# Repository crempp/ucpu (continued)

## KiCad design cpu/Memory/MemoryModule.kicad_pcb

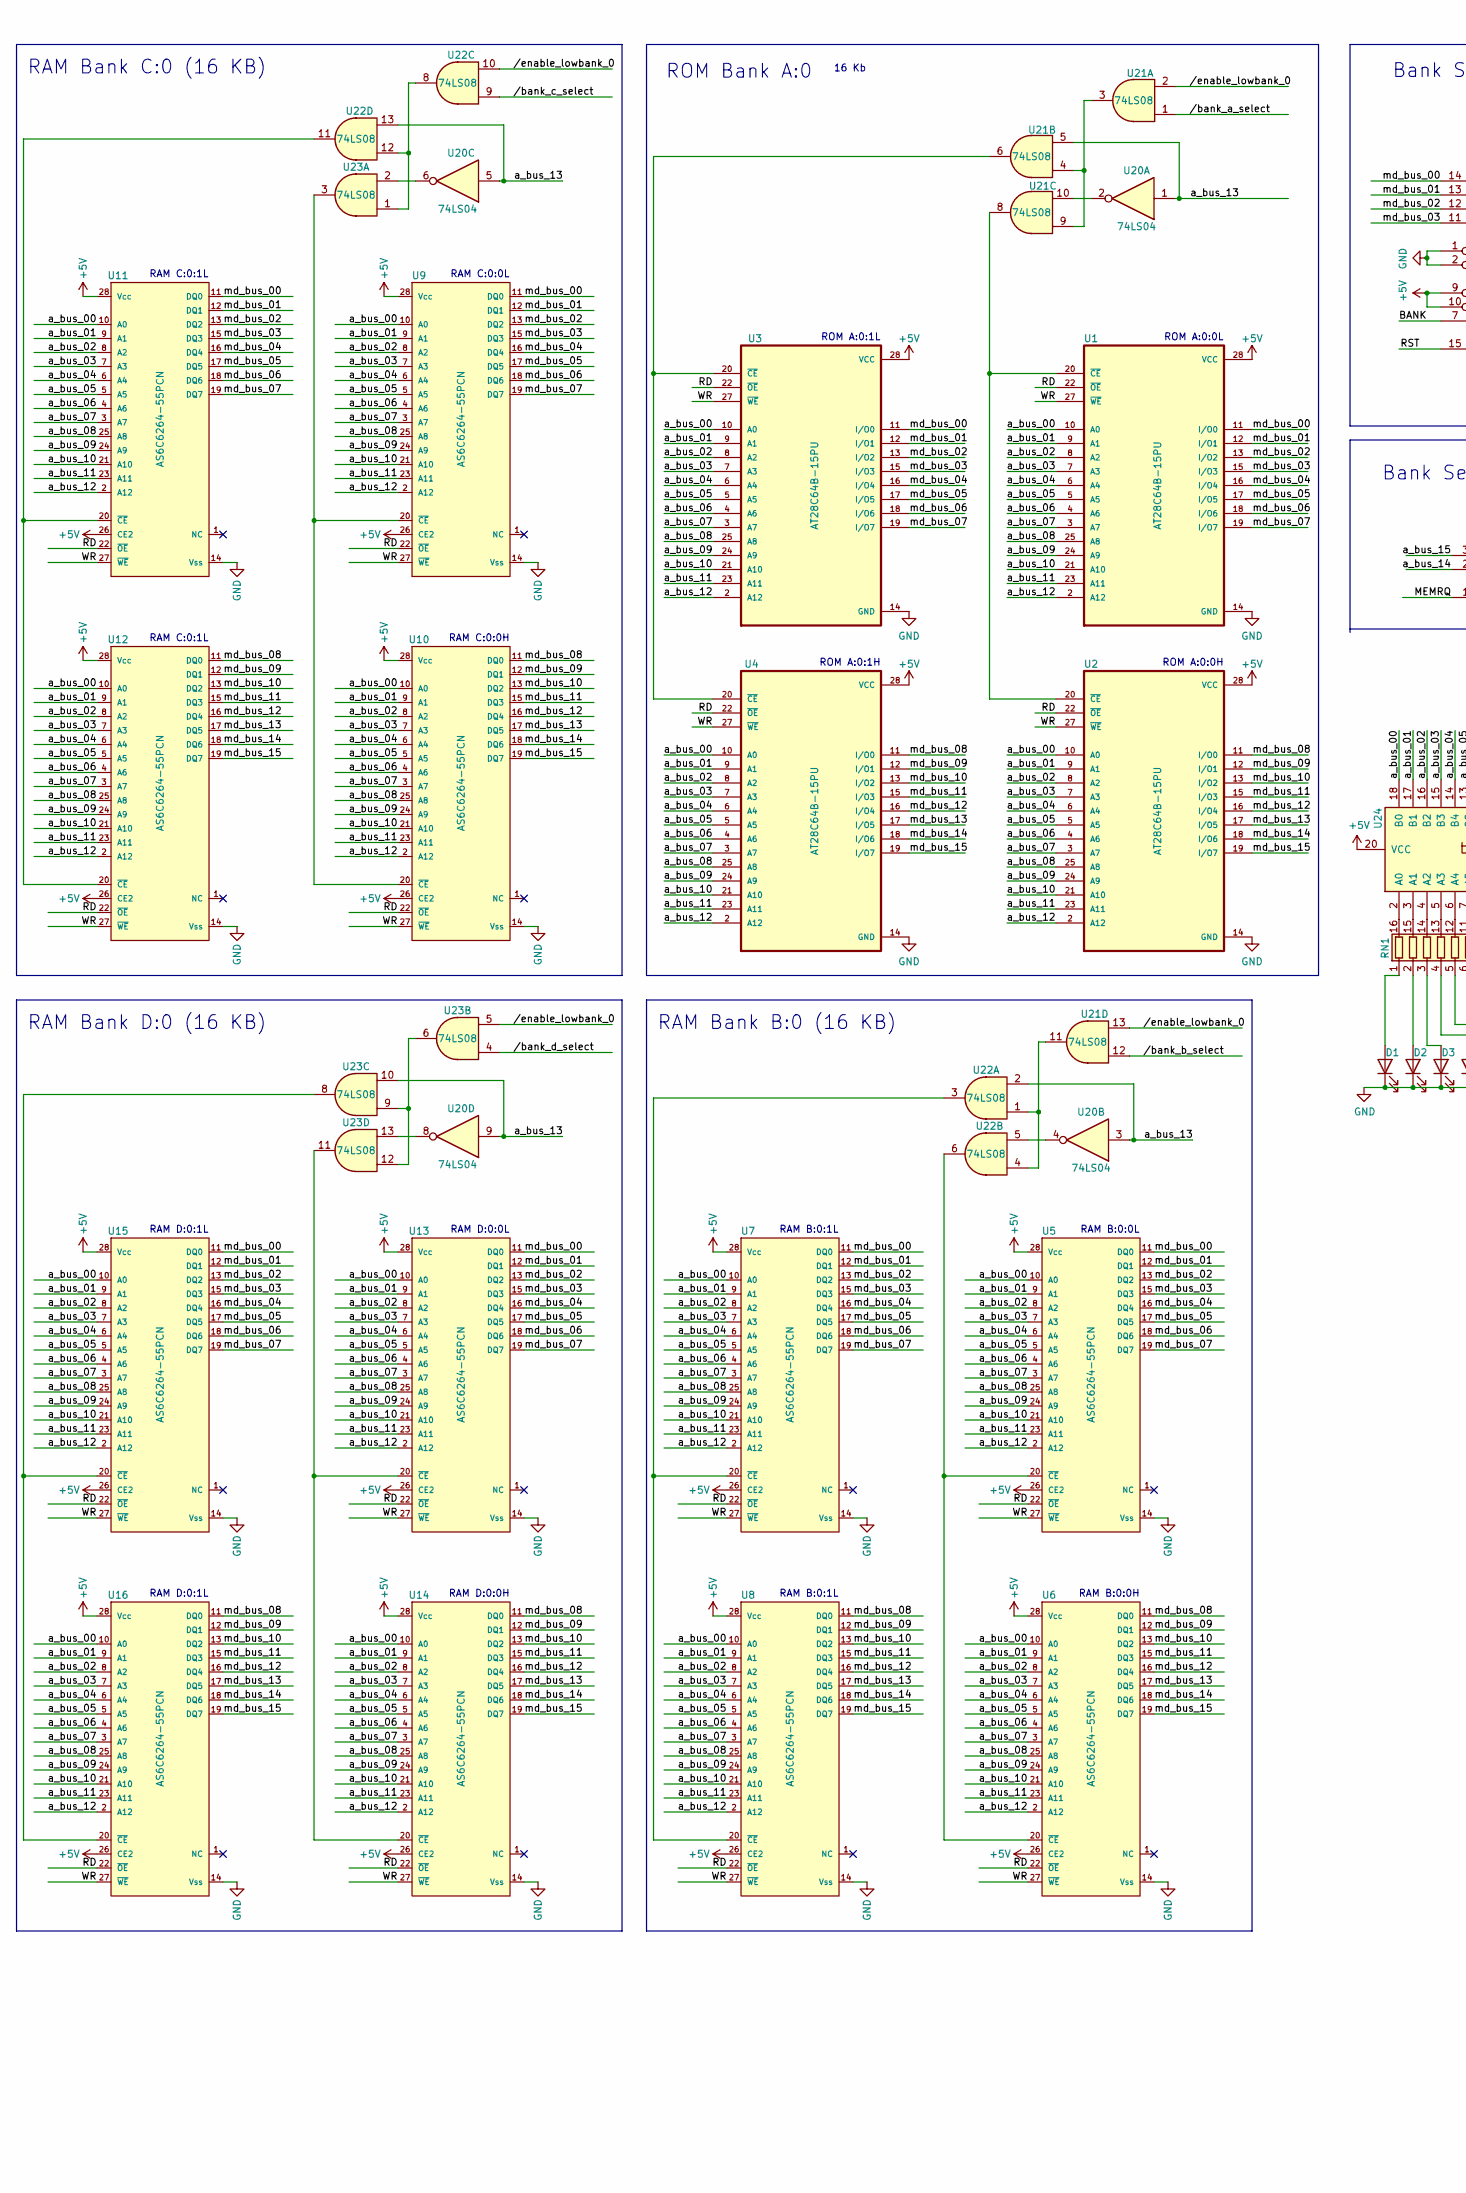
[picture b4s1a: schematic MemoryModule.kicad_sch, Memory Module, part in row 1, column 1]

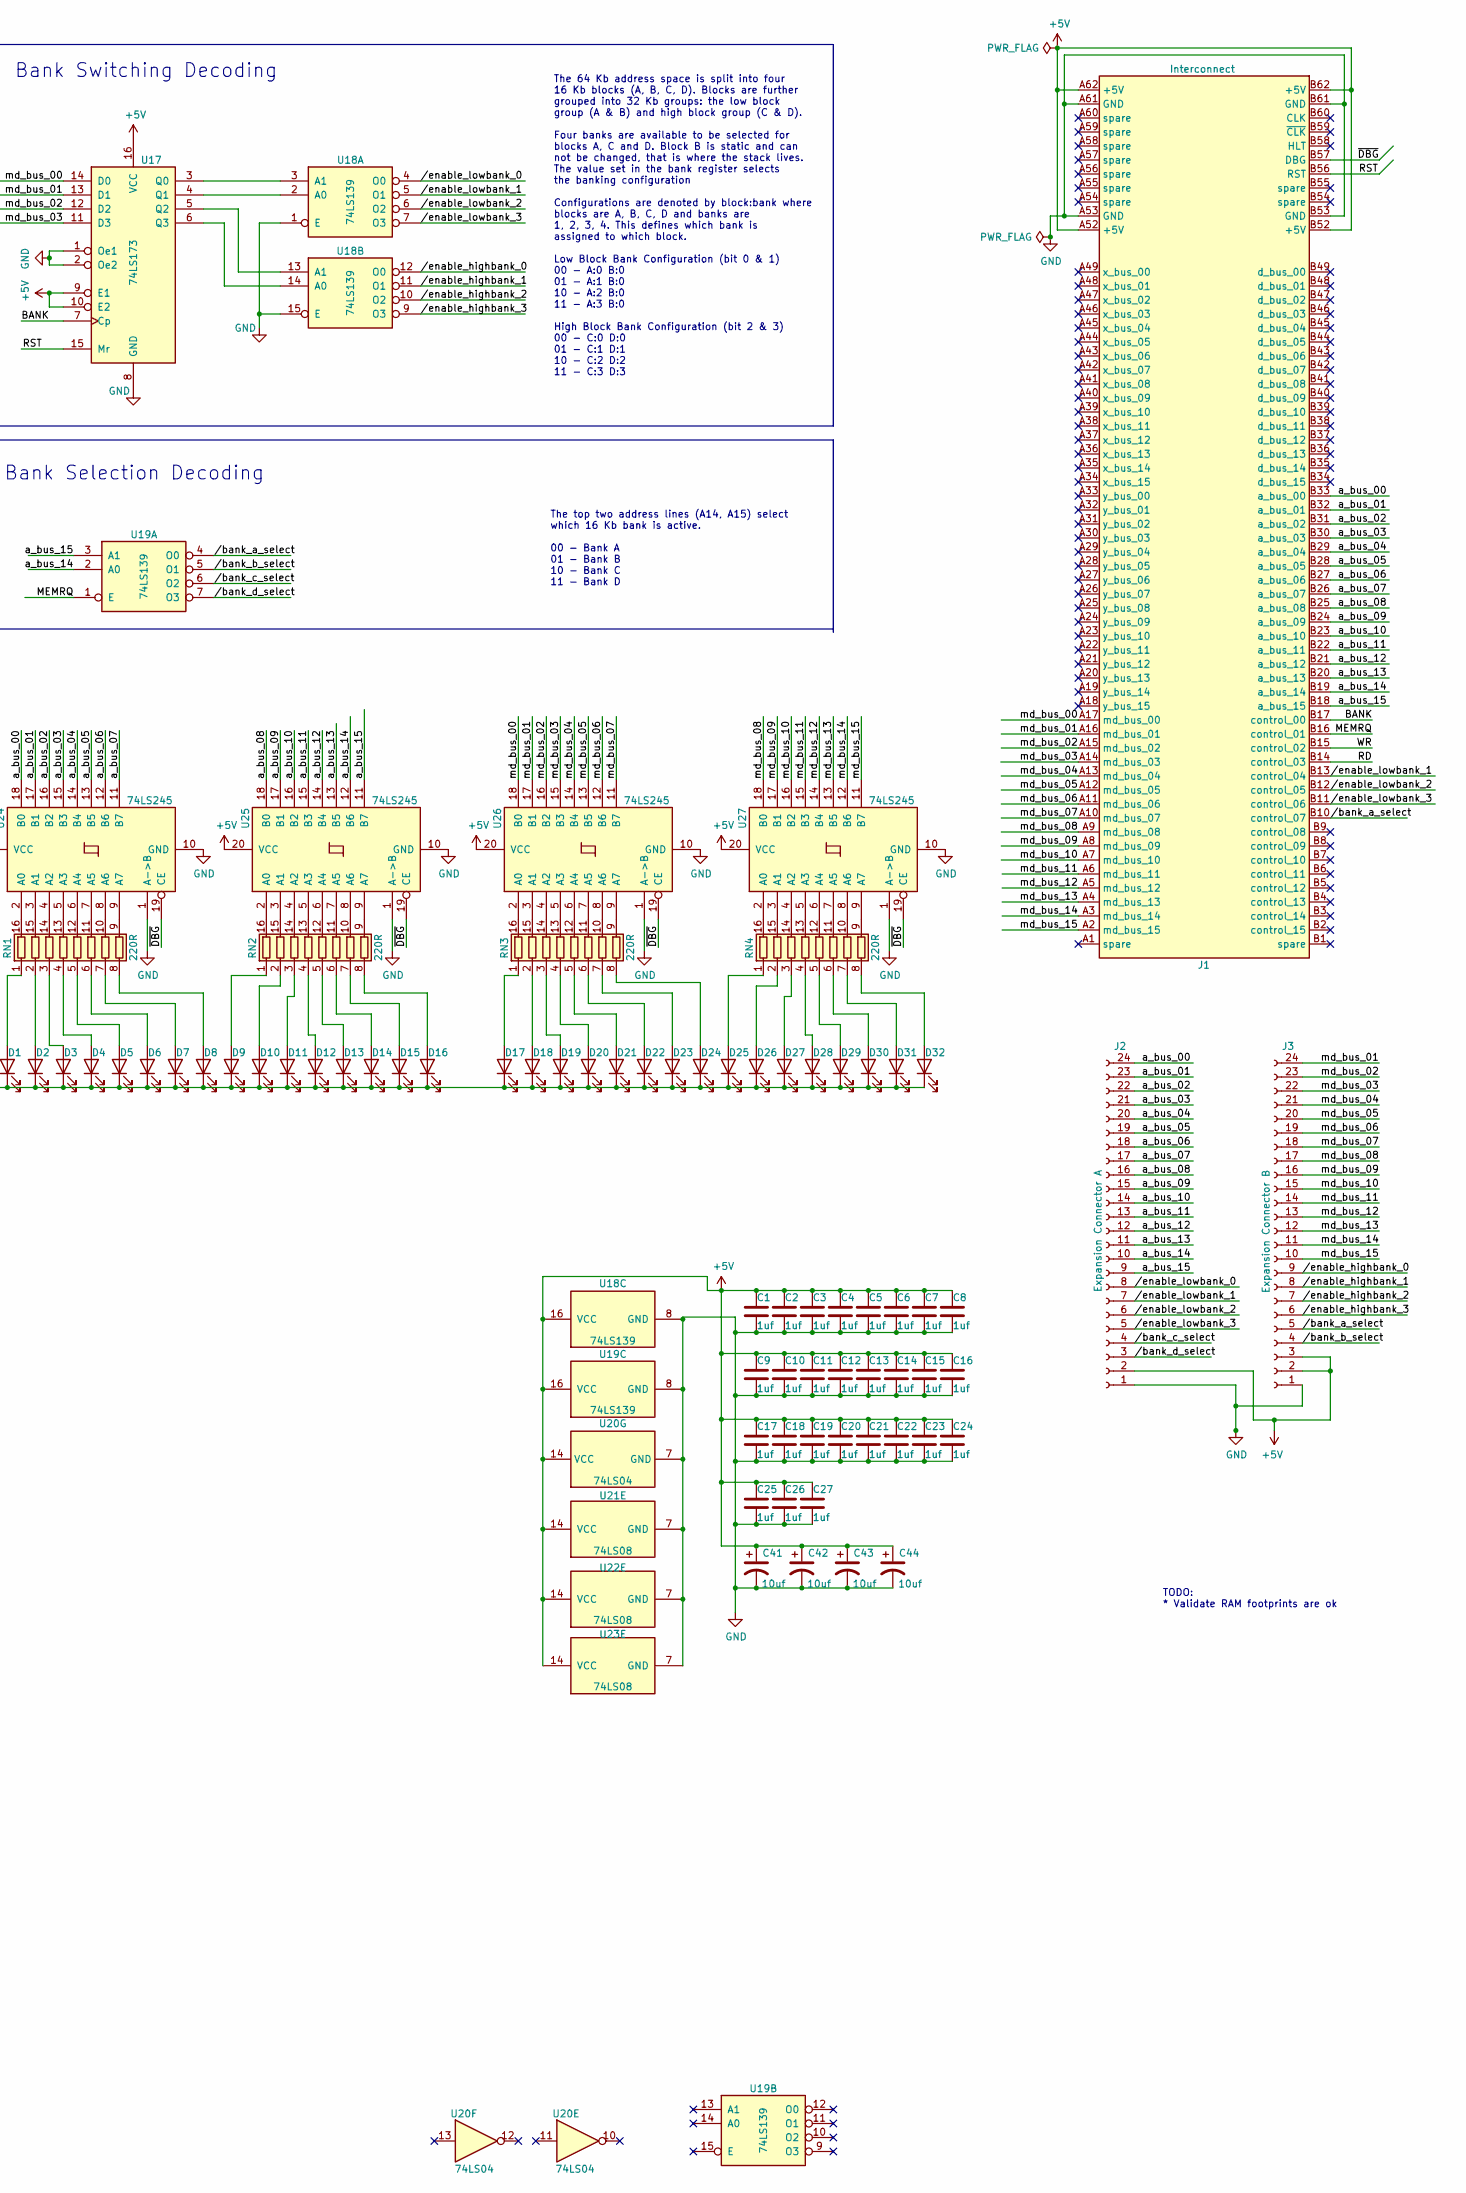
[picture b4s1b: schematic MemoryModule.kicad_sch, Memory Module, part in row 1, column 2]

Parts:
C1, C2, C3, C4, C5, C6, C7, C8, C9, C10, C11, C12, C13, C14, C15, C16, C17, C18, C19, C20, C21, C22, C23, C24, C25, C26, C27: 1uf; C_0603_1608Metric_Pad1.08x0.95mm_HandSolder
C41, C42, C43, C44: 10uf; CP_Elec_4x5.4
D1, D2, D3, D4, D5, D6, D7, D8, D9, D10, D11, D12, D13, D14, D15, D16, D17, D18, D19, D20, D21, D22, D23, D24, D25, D26, D27, D28, D29, D30, D31, D32: LED; LED_1206_3216Metric_Pad1.42x1.75mm_HandSolder
J1: Interconnect; BUS_PCI
J2: Expansion Connector A; PinHeader_1x24_P1.27mm_Vertical
J3: Expansion Connector B; PinHeader_1x24_P1.27mm_Vertical
RN1, RN2, RN3, RN4: 220R; R_Array_Convex_8x0602; Digikey Y1221CT-ND
U1, U2, U3, U4: AT28C64B-15PU; DIP-28_W15.24mm
U5, U6, U7, U8, U9, U10, U11, U12, U13, U14, U15, U16: AS6C6264-55PCN; SOIC-28W_7.5x18.7mm_P1.27mm; mouser part number 913-AS6C6264-55PCN; digikey description IC SRAM 64K PARALLEL 28DIP
U17: 74LS173; SOIC-16_3.9x9.9mm_P1.27mm
U18, U19: 74LS139; SOIC-16_3.9x9.9mm_P1.27mm
U20: 74LS04; SOIC-14_3.9x8.7mm_P1.27mm
U21, U22, U23: 74LS08; SOIC-14_3.9x8.7mm_P1.27mm
U24, U25, U26, U27: 74LS245; SOIC-20W_7.5x12.8mm_P1.27mm; Digikey 296-1208-1-ND

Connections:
+5V: C1.1, C2.1, C3.1, C4.1, C5.1, C6.1, C7.1, C8.1, C9.1, C10.1, C11.1, C12.1, C13.1, C14.1, C15.1, C16.1, C17.1, C18.1, C19.1, C20.1, C21.1, C22.1, C23.1, C24.1, C25.1, C26.1, C27.1, C41.1, C42.1, C43.1, C44.1, J1.A52 (+5V), J1.A62 (+5V), J1.B52 (+5V), J1.B62 (+5V), J2.2, J3.2, J3.3, U1.28 (VCC), U2.28 (VCC), U3.28 (VCC), U4.28 (VCC), U5.26 (CE2), U5.28 (Vcc), U6.26 (CE2), U6.28 (Vcc), U7.26 (CE2), U7.28 (Vcc), U8.26 (CE2), U8.28 (Vcc), U9.26 (CE2), U9.28 (Vcc), U10.26 (CE2), U10.28 (Vcc), U11.26 (CE2), U11.28 (Vcc), U12.26 (CE2), U12.28 (Vcc), U13.26 (CE2), U13.28 (Vcc), U14.26 (CE2), U14.28 (Vcc), U15.26 (CE2), U15.28 (Vcc), U16.26 (CE2), U16.28 (Vcc), U17.9 (E1), U17.10 (E2), U17.16 (VCC), U18.16 (VCC), U19.16 (VCC), U20.14 (VCC), U21.14 (VCC), U22.14 (VCC), U23.14 (VCC), U24.20 (VCC), U25.20 (VCC), U26.20 (VCC), U27.20 (VCC)
/BANK: J1.B17 (control_00), U17.7 (Cp)
/MEMRQ: J1.B16 (control_01), U19.1 (E)
/RD: J1.B14 (control_03), U1.22 (~OE), U2.22 (~OE), U3.22 (~OE), U4.22 (~OE), U5.22 (~OE), U6.22 (~OE), U7.22 (~OE), U8.22 (~OE), U9.22 (~OE), U10.22 (~OE), U11.22 (~OE), U12.22 (~OE), U13.22 (~OE), U14.22 (~OE), U15.22 (~OE), U16.22 (~OE)
/RST: J1.B56 (RST), U17.15 (Mr)
/WR: J1.B15 (control_02), U1.27 (~WE), U2.27 (~WE), U3.27 (~WE), U4.27 (~WE), U5.27 (~WE), U6.27 (~WE), U7.27 (~WE), U8.27 (~WE), U9.27 (~WE), U10.27 (~WE), U11.27 (~WE), U12.27 (~WE), U13.27 (~WE), U14.27 (~WE), U15.27 (~WE), U16.27 (~WE)
/a_bus_00: J1.B33 (a_bus_00), J2.24, U1.10 (A0), U2.10 (A0), U3.10 (A0), U4.10 (A0), U5.10 (A0), U6.10 (A0), U7.10 (A0), U8.10 (A0), U9.10 (A0), U10.10 (A0), U11.10 (A0), U12.10 (A0), U13.10 (A0), U14.10 (A0), U15.10 (A0), U16.10 (A0), U24.18 (B0)
/a_bus_01: J1.B32 (a_bus_01), J2.23, U1.9 (A1), U2.9 (A1), U3.9 (A1), U4.9 (A1), U5.9 (A1), U6.9 (A1), U7.9 (A1), U8.9 (A1), U9.9 (A1), U10.9 (A1), U11.9 (A1), U12.9 (A1), U13.9 (A1), U14.9 (A1), U15.9 (A1), U16.9 (A1), U24.17 (B1)
/a_bus_02: J1.B31 (a_bus_02), J2.22, U1.8 (A2), U2.8 (A2), U3.8 (A2), U4.8 (A2), U5.8 (A2), U6.8 (A2), U7.8 (A2), U8.8 (A2), U9.8 (A2), U10.8 (A2), U11.8 (A2), U12.8 (A2), U13.8 (A2), U14.8 (A2), U15.8 (A2), U16.8 (A2), U24.16 (B2)
/a_bus_03: J1.B30 (a_bus_03), J2.21, U1.7 (A3), U2.7 (A3), U3.7 (A3), U4.7 (A3), U5.7 (A3), U6.7 (A3), U7.7 (A3), U8.7 (A3), U9.7 (A3), U10.7 (A3), U11.7 (A3), U12.7 (A3), U13.7 (A3), U14.7 (A3), U15.7 (A3), U16.7 (A3), U24.15 (B3)
/a_bus_04: J1.B29 (a_bus_04), J2.20, U1.6 (A4), U2.6 (A4), U3.6 (A4), U4.6 (A4), U5.6 (A4), U6.6 (A4), U7.6 (A4), U8.6 (A4), U9.6 (A4), U10.6 (A4), U11.6 (A4), U12.6 (A4), U13.6 (A4), U14.6 (A4), U15.6 (A4), U16.6 (A4), U24.14 (B4)
/a_bus_05: J1.B28 (a_bus_05), J2.19, U1.5 (A5), U2.5 (A5), U3.5 (A5), U4.5 (A5), U5.5 (A5), U6.5 (A5), U7.5 (A5), U8.5 (A5), U9.5 (A5), U10.5 (A5), U11.5 (A5), U12.5 (A5), U13.5 (A5), U14.5 (A5), U15.5 (A5), U16.5 (A5), U24.13 (B5)
/a_bus_06: J1.B27 (a_bus_06), J2.18, U1.4 (A6), U2.4 (A6), U3.4 (A6), U4.4 (A6), U5.4 (A6), U6.4 (A6), U7.4 (A6), U8.4 (A6), U9.4 (A6), U10.4 (A6), U11.4 (A6), U12.4 (A6), U13.4 (A6), U14.4 (A6), U15.4 (A6), U16.4 (A6), U24.12 (B6)
/a_bus_07: J1.B26 (a_bus_07), J2.17, U1.3 (A7), U2.3 (A7), U3.3 (A7), U4.3 (A7), U5.3 (A7), U6.3 (A7), U7.3 (A7), U8.3 (A7), U9.3 (A7), U10.3 (A7), U11.3 (A7), U12.3 (A7), U13.3 (A7), U14.3 (A7), U15.3 (A7), U16.3 (A7), U24.11 (B7)
/a_bus_08: J1.B25 (a_bus_08), J2.16, U1.25 (A8), U2.25 (A8), U3.25 (A8), U4.25 (A8), U5.25 (A8), U6.25 (A8), U7.25 (A8), U8.25 (A8), U9.25 (A8), U10.25 (A8), U11.25 (A8), U12.25 (A8), U13.25 (A8), U14.25 (A8), U15.25 (A8), U16.25 (A8), U25.18 (B0)
/a_bus_09: J1.B24 (a_bus_09), J2.15, U1.24 (A9), U2.24 (A9), U3.24 (A9), U4.24 (A9), U5.24 (A9), U6.24 (A9), U7.24 (A9), U8.24 (A9), U9.24 (A9), U10.24 (A9), U11.24 (A9), U12.24 (A9), U13.24 (A9), U14.24 (A9), U15.24 (A9), U16.24 (A9), U25.17 (B1)
/a_bus_10: J1.B23 (a_bus_10), J2.14, U1.21 (A10), U2.21 (A10), U3.21 (A10), U4.21 (A10), U5.21 (A10), U6.21 (A10), U7.21 (A10), U8.21 (A10), U9.21 (A10), U10.21 (A10), U11.21 (A10), U12.21 (A10), U13.21 (A10), U14.21 (A10), U15.21 (A10), U16.21 (A10), U25.16 (B2)
/a_bus_11: J1.B22 (a_bus_11), J2.13, U1.23 (A11), U2.23 (A11), U3.23 (A11), U4.23 (A11), U5.23 (A11), U6.23 (A11), U7.23 (A11), U8.23 (A11), U9.23 (A11), U10.23 (A11), U11.23 (A11), U12.23 (A11), U13.23 (A11), U14.23 (A11), U15.23 (A11), U16.23 (A11), U25.15 (B3)
/a_bus_12: J1.B21 (a_bus_12), J2.12, U1.2 (A12), U2.2 (A12), U3.2 (A12), U4.2 (A12), U5.2 (A12), U6.2 (A12), U7.2 (A12), U8.2 (A12), U9.2 (A12), U10.2 (A12), U11.2 (A12), U12.2 (A12), U13.2 (A12), U14.2 (A12), U15.2 (A12), U16.2 (A12), U25.14 (B4)
/a_bus_13: J1.B20 (a_bus_13), J2.11, U20.1, U20.3, U20.5, U20.9, U21.5, U22.2, U22.13, U23.10, U25.13 (B5)
/a_bus_14: J1.B19 (a_bus_14), J2.10, U19.2 (A0), U25.12 (B6)
/a_bus_15: J1.B18 (a_bus_15), J2.9, U19.3 (A1), U25.11 (B7)
/md_bus_00: J1.A17 (md_bus_00), U1.11 (I/O0), U3.11 (I/O0), U5.11 (DQ0), U7.11 (DQ0), U9.11 (DQ0), U11.11 (DQ0), U13.11 (DQ0), U15.11 (DQ0), U17.14 (D0), U26.18 (B0)
/md_bus_01: J1.A16 (md_bus_01), J3.24, U1.12 (I/O1), U3.12 (I/O1), U5.12 (DQ1), U7.12 (DQ1), U9.12 (DQ1), U11.12 (DQ1), U13.12 (DQ1), U15.12 (DQ1), U17.13 (D1), U26.17 (B1)
/md_bus_02: J1.A15 (md_bus_02), J3.23, U1.13 (I/O2), U3.13 (I/O2), U5.13 (DQ2), U7.13 (DQ2), U9.13 (DQ2), U11.13 (DQ2), U13.13 (DQ2), U15.13 (DQ2), U17.12 (D2), U26.16 (B2)
/md_bus_03: J1.A14 (md_bus_03), J3.22, U1.15 (I/O3), U3.15 (I/O3), U5.15 (DQ3), U7.15 (DQ3), U9.15 (DQ3), U11.15 (DQ3), U13.15 (DQ3), U15.15 (DQ3), U17.11 (D3), U26.15 (B3)
/md_bus_04: J1.A13 (md_bus_04), J3.21, U1.16 (I/O4), U3.16 (I/O4), U5.16 (DQ4), U7.16 (DQ4), U9.16 (DQ4), U11.16 (DQ4), U13.16 (DQ4), U15.16 (DQ4), U26.14 (B4)
/md_bus_05: J1.A12 (md_bus_05), J3.20, U1.17 (I/O5), U3.17 (I/O5), U5.17 (DQ5), U7.17 (DQ5), U9.17 (DQ5), U11.17 (DQ5), U13.17 (DQ5), U15.17 (DQ5), U26.13 (B5)
/md_bus_06: J1.A11 (md_bus_06), J3.19, U1.18 (I/O6), U3.18 (I/O6), U5.18 (DQ6), U7.18 (DQ6), U9.18 (DQ6), U11.18 (DQ6), U13.18 (DQ6), U15.18 (DQ6), U26.12 (B6)
/md_bus_07: J1.A10 (md_bus_07), J3.18, U1.19 (I/O7), U3.19 (I/O7), U5.19 (DQ7), U7.19 (DQ7), U9.19 (DQ7), U11.19 (DQ7), U13.19 (DQ7), U15.19 (DQ7), U26.11 (B7)
/md_bus_08: J1.A9 (md_bus_08), J3.17, U2.11 (I/O0), U4.11 (I/O0), U6.11 (DQ0), U8.11 (DQ0), U10.11 (DQ0), U12.11 (DQ0), U14.11 (DQ0), U16.11 (DQ0), U27.18 (B0)
/md_bus_09: J1.A8 (md_bus_09), J3.16, U2.12 (I/O1), U4.12 (I/O1), U6.12 (DQ1), U8.12 (DQ1), U10.12 (DQ1), U12.12 (DQ1), U14.12 (DQ1), U16.12 (DQ1), U27.17 (B1)
/md_bus_10: J1.A7 (md_bus_10), J3.15, U2.13 (I/O2), U4.13 (I/O2), U6.13 (DQ2), U8.13 (DQ2), U10.13 (DQ2), U12.13 (DQ2), U14.13 (DQ2), U16.13 (DQ2), U27.16 (B2)
/md_bus_11: J1.A6 (md_bus_11), J3.14, U2.15 (I/O3), U4.15 (I/O3), U6.15 (DQ3), U8.15 (DQ3), U10.15 (DQ3), U12.15 (DQ3), U14.15 (DQ3), U16.15 (DQ3), U27.15 (B3)
/md_bus_12: J1.A5 (md_bus_12), J3.13, U2.16 (I/O4), U4.16 (I/O4), U6.16 (DQ4), U8.16 (DQ4), U10.16 (DQ4), U12.16 (DQ4), U14.16 (DQ4), U16.16 (DQ4), U27.14 (B4)
/md_bus_13: J1.A4 (md_bus_13), J3.12, U2.17 (I/O5), U4.17 (I/O5), U6.17 (DQ5), U8.17 (DQ5), U10.17 (DQ5), U12.17 (DQ5), U14.17 (DQ5), U16.17 (DQ5), U27.13 (B5)
/md_bus_14: J1.A3 (md_bus_14), J3.11, U2.18 (I/O6), U4.18 (I/O6), U6.18 (DQ6), U8.18 (DQ6), U10.18 (DQ6), U12.18 (DQ6), U14.18 (DQ6), U16.18 (DQ6), U27.12 (B6)
/md_bus_15: J1.A2 (md_bus_15), J3.10, U2.19 (I/O7), U4.19 (I/O7), U6.19 (DQ7), U8.19 (DQ7), U10.19 (DQ7), U12.19 (DQ7), U14.19 (DQ7), U16.19 (DQ7), U27.11 (B7)
//bank_a_select: J1.B10 (control_07), J3.5, U19.4 (O0), U21.1
//bank_c_select: J2.4, U19.6 (O2), U22.9
//bank_d_select: J2.3, U19.7 (O3), U23.4
//enable_highbank_1: J3.8, U18.11 (O1)
//enable_highbank_2: J3.7, U18.10 (O2)
//enable_highbank_3: J3.6, U18.9 (O3)
//enable_lowbank_1: J1.B13 (control_04), J2.7, U18.5 (O1)
//enable_lowbank_2: J1.B12 (control_05), J2.6, U18.6 (O2)
//enable_lowbank_3: J1.B11 (control_06), J2.5, U18.7 (O3)
/~DBG: J1.B57 (DBG), U24.19 (CE), U25.19 (CE), U26.19 (CE), U27.19 (CE)
GND: C1.2, C2.2, C3.2, C4.2, C5.2, C6.2, C7.2, C8.2, C9.2, C10.2, C11.2, C12.2, C13.2, C14.2, C15.2, C16.2, C17.2, C18.2, C19.2, C20.2, C21.2, C22.2, C23.2, C24.2, C25.2, C26.2, C27.2, C41.2, C42.2, C43.2, C44.2, D1.1 (K), D2.1 (K), D3.1 (K), D4.1 (K), D5.1 (K), D6.1 (K), D7.1 (K), D8.1 (K), D9.1 (K), D10.1 (K), D11.1 (K), D12.1 (K), D13.1 (K), D14.1 (K), D15.1 (K), D16.1 (K), D17.1 (K), D18.1 (K), D19.1 (K), D20.1 (K), D21.1 (K), D22.1 (K), D23.1 (K), D24.1 (K), D25.1 (K), D26.1 (K), D27.1 (K), D28.1 (K), D29.1 (K), D30.1 (K), D31.1 (K), D32.1 (K), J1.A53 (GND), J1.A61 (GND), J1.B53 (GND), J1.B61 (GND), J2.1, J3.1, U1.14 (GND), U2.14 (GND), U3.14 (GND), U4.14 (GND), U5.14 (Vss), U6.14 (Vss), U7.14 (Vss), U8.14 (Vss), U9.14 (Vss), U10.14 (Vss), U11.14 (Vss), U12.14 (Vss), U13.14 (Vss), U14.14 (Vss), U15.14 (Vss), U16.14 (Vss), U17.1 (Oe1), U17.2 (Oe2), U17.8 (GND), U18.1 (E), U18.8 (GND), U18.15 (E), U19.8 (GND), U20.7 (GND), U21.7 (GND), U22.7 (GND), U23.7 (GND), U24.1 (A->B), U24.10 (GND), U25.1 (A->B), U25.10 (GND), U26.1 (A->B), U26.10 (GND), U27.1 (A->B), U27.10 (GND)
unnamed: D1.2 (A), RN1.1 (R1.1)
unnamed: D2.2 (A), RN1.2 (R2.1)
unnamed: D3.2 (A), RN1.3 (R3.1)
unnamed: D4.2 (A), RN1.4 (R4.1)
unnamed: D5.2 (A), RN1.5 (R5.1)
unnamed: D6.2 (A), RN1.6 (R6.1)
unnamed: D7.2 (A), RN1.7 (R7.1)
unnamed: D8.2 (A), RN1.8 (R8.1)
unnamed: D9.2 (A), RN2.1 (R1.1)
unnamed: D10.2 (A), RN2.2 (R2.1)
unnamed: D11.2 (A), RN2.3 (R3.1)
unnamed: D12.2 (A), RN2.4 (R4.1)
unnamed: D13.2 (A), RN2.5 (R5.1)
unnamed: D14.2 (A), RN2.6 (R6.1)
unnamed: D15.2 (A), RN2.7 (R7.1)
unnamed: D16.2 (A), RN2.8 (R8.1)
unnamed: D17.2 (A), RN3.1 (R1.1)
unnamed: D18.2 (A), RN3.2 (R2.1)
unnamed: D19.2 (A), RN3.3 (R3.1)
unnamed: D20.2 (A), RN3.4 (R4.1)
unnamed: D21.2 (A), RN3.5 (R5.1)
unnamed: D22.2 (A), RN3.6 (R6.1)
unnamed: D23.2 (A), RN3.7 (R7.1)
unnamed: D24.2 (A), RN3.8 (R8.1)
unnamed: D25.2 (A), RN4.1 (R1.1)
unnamed: D26.2 (A), RN4.2 (R2.1)
unnamed: D27.2 (A), RN4.3 (R3.1)
unnamed: D28.2 (A), RN4.4 (R4.1)
unnamed: D29.2 (A), RN4.5 (R5.1)
unnamed: D30.2 (A), RN4.6 (R6.1)
unnamed: D31.2 (A), RN4.7 (R7.1)
unnamed: D32.2 (A), RN4.8 (R8.1)
unnamed: RN1.9 (R8.2), U24.9 (A7)
unnamed: RN1.10 (R7.2), U24.8 (A6)
unnamed: RN1.11 (R6.2), U24.7 (A5)
unnamed: RN1.12 (R5.2), U24.6 (A4)
unnamed: RN1.13 (R4.2), U24.5 (A3)
unnamed: RN1.14 (R3.2), U24.4 (A2)
unnamed: RN1.15 (R2.2), U24.3 (A1)
unnamed: RN1.16 (R1.2), U24.2 (A0)
unnamed: RN2.9 (R8.2), U25.9 (A7)
unnamed: RN2.10 (R7.2), U25.8 (A6)
unnamed: RN2.11 (R6.2), U25.7 (A5)
unnamed: RN2.12 (R5.2), U25.6 (A4)
unnamed: RN2.13 (R4.2), U25.5 (A3)
unnamed: RN2.14 (R3.2), U25.4 (A2)
unnamed: RN2.15 (R2.2), U25.3 (A1)
unnamed: RN2.16 (R1.2), U25.2 (A0)
unnamed: RN3.9 (R8.2), U26.9 (A7)
unnamed: RN3.10 (R7.2), U26.8 (A6)
unnamed: RN3.11 (R6.2), U26.7 (A5)
unnamed: RN3.12 (R5.2), U26.6 (A4)
unnamed: RN3.13 (R4.2), U26.5 (A3)
unnamed: RN3.14 (R3.2), U26.4 (A2)
unnamed: RN3.15 (R2.2), U26.3 (A1)
unnamed: RN3.16 (R1.2), U26.2 (A0)
unnamed: RN4.9 (R8.2), U27.9 (A7)
unnamed: RN4.10 (R7.2), U27.8 (A6)
unnamed: RN4.11 (R6.2), U27.7 (A5)
unnamed: RN4.12 (R5.2), U27.6 (A4)
unnamed: RN4.13 (R4.2), U27.5 (A3)
unnamed: RN4.14 (R3.2), U27.4 (A2)
unnamed: RN4.15 (R2.2), U27.3 (A1)
unnamed: RN4.16 (R1.2), U27.2 (A0)
unnamed: U1.20 (~CE), U2.20 (~CE), U21.8
unnamed: U9.20 (~CE), U10.20 (~CE), U23.3
unnamed: U11.20 (~CE), U12.20 (~CE), U22.11
unnamed: U13.20 (~CE), U14.20 (~CE), U23.11
unnamed: U15.20 (~CE), U16.20 (~CE), U23.8
unnamed: U17.3 (Q0), U18.3 (A1)
unnamed: U17.4 (Q1), U18.2 (A0)
unnamed: U17.5 (Q2), U18.13 (A1)
unnamed: U17.6 (Q3), U18.14 (A0)
unnamed: U20.2, U21.10
unnamed: U20.4, U22.5
unnamed: U20.6, U23.2
unnamed: U20.8, U23.13
unnamed: U21.3, U21.4, U21.9
unnamed: U3.20 (~CE), U4.20 (~CE), U21.6
unnamed: U7.20 (~CE), U8.20 (~CE), U22.3
unnamed: U5.20 (~CE), U6.20 (~CE), U22.6
unnamed: U22.8, U22.12, U23.1
unnamed: U23.6, U23.9, U23.12

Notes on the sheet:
RAM D:0:0L
ROM A:0:1L
The top two address lines (A14, A15) select which 16 Kb bank is active. 00 - Bank A 01 - Bank B 10 - Bank C 11 - Bank D
The 64 Kb address space is split into four 16 Kb blocks (A, B, C, D). Blocks are further grouped into 32 Kb groups: the low block group (A & B) and high block group (C & D). Four banks are available to be selected for blocks A, C and D. Block B is static and can not be changed, that is where the st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
RAM D:0:1L
Bank Selection Decoding
ROM A:0:0L
ROM Bank A:0
RAM C:0:1L
RAM Bank C:0 (16 KB)
Bank Switching Decoding
RAM Bank D:0 (16 KB)
RAM C:0:0H
RAM B:0:1L
RAM B:0:0L
RAM D:0:0H
ROM A:0:0H
RAM C:0:0L
RAM Bank B:0 (16 KB)
TODO: * Validate RAM footprints are ok
16 Kb
ROM A:0:1H
RAM B:0:0H

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
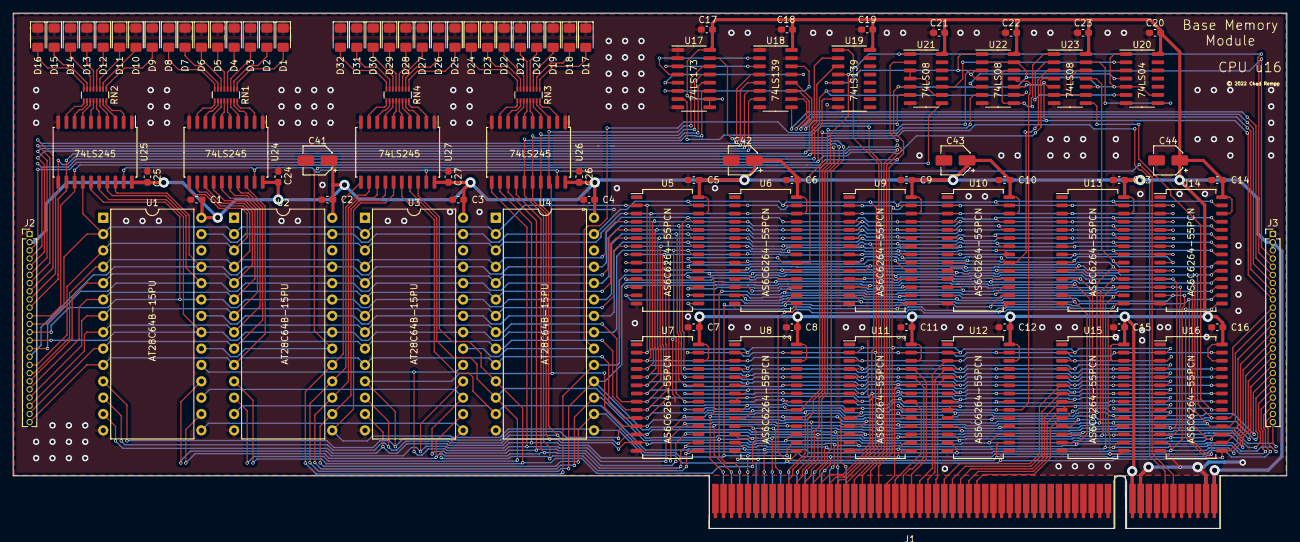
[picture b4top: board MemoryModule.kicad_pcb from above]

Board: 2 copper layers, 197.8 x 80.0 mm, 97 parts (0 on the bottom side), 135 nets.

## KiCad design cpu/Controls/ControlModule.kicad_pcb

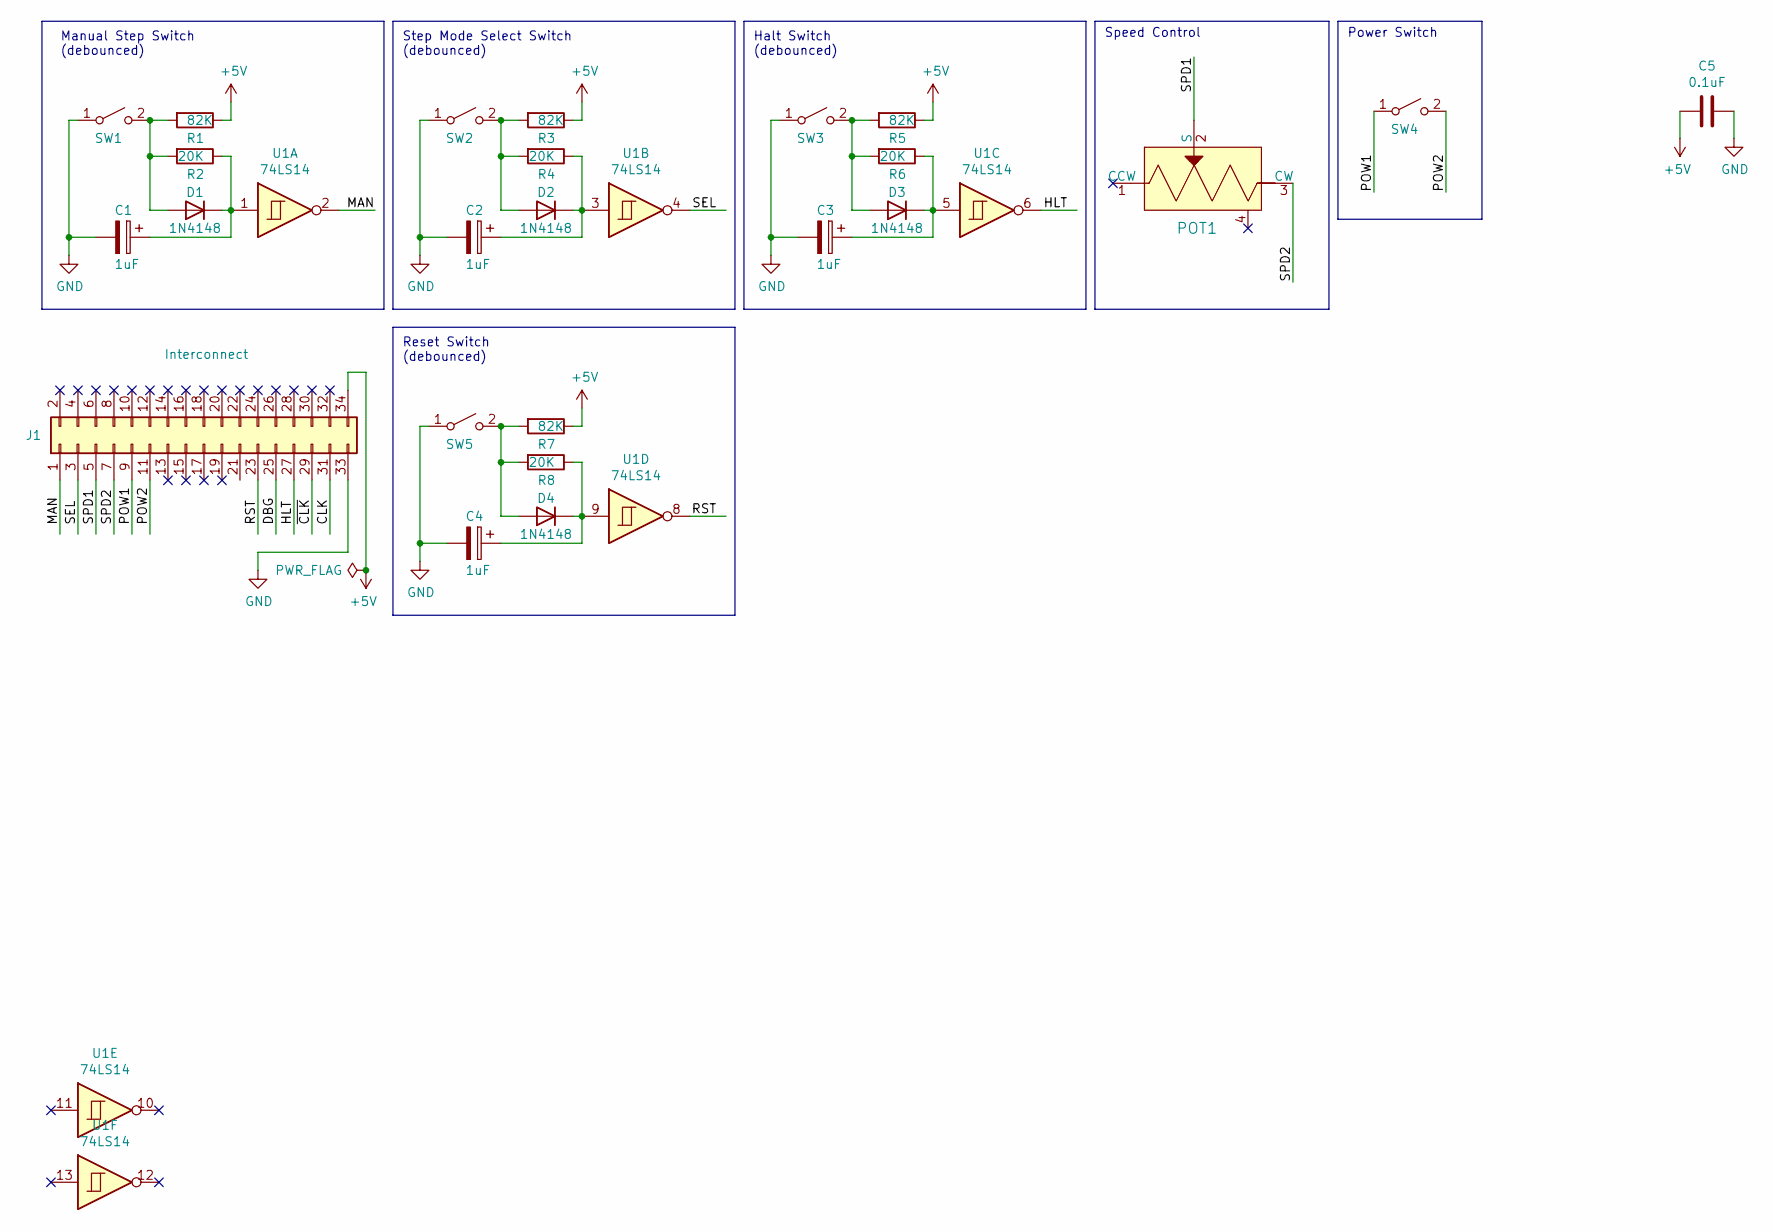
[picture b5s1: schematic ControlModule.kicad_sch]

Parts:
C1, C2, C3, C4: 1uF; CP_Elec_4x5.4; Digikey 493-9795-1-ND
C5: 0.1uF; C_0603_1608Metric_Pad1.05x0.95mm_HandSolder; Digikey 399-1096-1-ND
D1, D2, D3, D4: 1N4148; D_SOD-523; Digikey 1N4148XTPMSCT-ND
J1: Interconnect; PinHeader_2x17_P2.54mm_Horizontal; Digikey S5531-ND
POT1: P120PK-Y25BR10K; Potentiometer_P120PK-Y25BR10K; MPN P120PK-Y25BR10K; Digi-Key_PN 987-1710-ND
R1, R3, R5, R7: 82K; R_0603_1608Metric_Pad1.05x0.95mm_HandSolder; Digikey 311-82.0KHRCT-ND
R2, R4, R6, R8: 20K; R_0603_1608Metric_Pad1.05x0.95mm_HandSolder; Digikey 311-20.0KHRCT-ND
SW1, SW3, SW5: SW_SPST; SW_PUSH_6mm_H5mm; Digikey EG1861-ND
SW2, SW4: SW_SPST; SW_PUSH_6mm_H5mm; Digikey 401-1132-ND
U1: 74LS14; SOIC-14_3.9x8.7mm_P1.27mm; Digikey 296-14864-1-ND

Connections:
+5V: C5.2, J1.34, R1.1, R3.1, R5.1, R7.1
/CLK: J1.31
/DBG: J1.25
/HLT: J1.27, U1.6
/MAN: J1.1, U1.2
/POW1: J1.9, SW4.1 (A)
/POW2: J1.11, SW4.2 (B)
/RST: J1.23, U1.8
/SEL: J1.3, U1.4
/SPD1: J1.5, POT1.2 (S)
/SPD2: J1.7, POT1.3 (CW)
/~CLK: J1.29
GND: C1.2, C2.2, C3.2, C4.2, C5.1, J1.33, SW1.1 (A), SW2.1 (A), SW3.1 (A), SW5.1 (A)
unnamed: C1.1, D1.1 (K), R2.1, U1.1
unnamed: C2.1, D2.1 (K), R4.1, U1.3
unnamed: C3.1, D3.1 (K), R6.1, U1.5
unnamed: C4.1, D4.1 (K), R8.1, U1.9
unnamed: D1.2 (A), R1.2, R2.2, SW1.2 (B)
unnamed: D2.2 (A), R3.2, R4.2, SW2.2 (B)
unnamed: D3.2 (A), R5.2, R6.2, SW3.2 (B)
unnamed: D4.2 (A), R7.2, R8.2, SW5.2 (B)

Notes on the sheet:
Halt Switch (debounced)
Step Mode Select Switch (debounced)
Manual Step Switch (debounced)
Reset Switch (debounced)
Power Switch
Speed Control

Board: 2 copper layers, 25 parts (0 on the bottom side), 18 nets, no tracks yet.

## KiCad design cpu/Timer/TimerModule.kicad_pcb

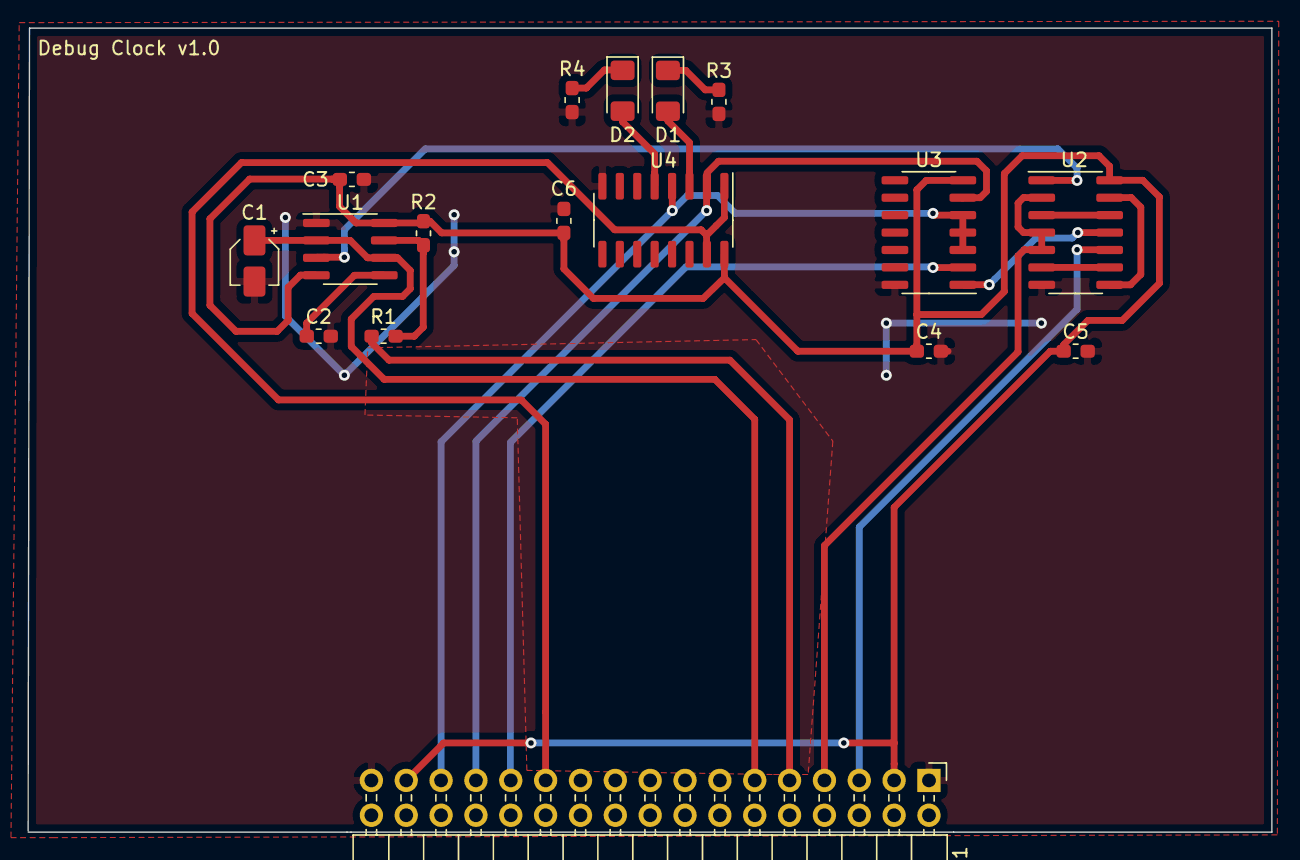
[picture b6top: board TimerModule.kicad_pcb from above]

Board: 2 copper layers, 90.6 x 58.6 mm, 17 parts (0 on the bottom side), 21 nets.

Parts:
C1: 1uF; CP_Elec_3x5.4
C2: 0.01uF; C_0603_1608Metric_Pad1.05x0.95mm_HandSolder
C3, C4, C5, C6: 0.1uF; C_0603_1608Metric_Pad1.05x0.95mm_HandSolder
D1: ~{CLK}; LED_1206_3216Metric_Pad1.42x1.75mm_HandSolder
D2: CLK; LED_1206_3216Metric_Pad1.42x1.75mm_HandSolder
J1: Interconnect; PinHeader_2x17_P2.54mm_Horizontal
R1: 100R; R_0603_1608Metric_Pad1.05x0.95mm_HandSolder
R2: 1K; R_0603_1608Metric_Pad1.05x0.95mm_HandSolder
R3, R4: 220R; R_0603_1608Metric_Pad1.05x0.95mm_HandSolder
U1: LM555; SOIC-8_3.9x4.9mm_P1.27mm
U2, U3: 74LS00; SOIC-14_3.9x8.7mm_P1.27mm
U4: 74LS365; SOIC-16_3.9x9.9mm_P1.27mm

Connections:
+5V: C3.1, C4.1, C5.1, C6.1, J1.3, J1.31, R2.2, U1.4, U1.8, U2.14, U3.7, U4.16
CLK: J1.29, U3.3, U3.4, U3.5, U4.4
DBG: J1.23, U4.1, U4.15
GND: C1.2, C2.2, C3.2, C4.2, C5.2, C6.2, J1.1, J1.33, R3.1, R4.1, U1.1, U2.7, U3.14, U4.8
HLT: J1.25, U3.2
MAN: J1.5, U2.10
unnamed: C2.1, U1.5
unnamed: D1.1, R3.2
unnamed: D1.2, U4.3
unnamed: D2.1, R4.2
unnamed: D2.2, U4.5
unnamed: R1.2, R2.1, U1.7
unnamed: U1.3, U2.1
unnamed: U2.6, U2.9
unnamed: U2.11, U3.1
unnamed: U2.3, U2.12
unnamed: U2.8, U2.13
SEL: J1.7, U2.2, U2.4, U2.5
SPD1: J1.9, R1.1
SPD2: C1.1, J1.11, U1.2, U1.6
~CLK: J1.27, U3.6, U4.2
